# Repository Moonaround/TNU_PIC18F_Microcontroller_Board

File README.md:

# TNU PIC18F Microcontroller Board Replication

## Project Overview
This repository contains the engineering design files to replicate the **TNU PIC18F Microcontroller Board** for the Microcontrollers course footprint project. 

## Technical Specifications
* **Target Architecture:** PIC18F 40-Pin Microcontroller variant
* **Design Toolchain:** KiCad 8.0 (Ubuntu Linux environment)
* **Source Reference Assets:** 
  * Schematic Specifications: `Cadence_Pic40_TNU_PCB_schematic_v2.pdf`
  * Inventory Component Ledger: `Cadence_Pic40_TNU_Bill_Of_Material.xlsx`

## Engineering Phase Progression Log
* [x] **Phase 1-2:** Repository initialization and hardware tracking rules configuration.
* [x] **Phase 3-4:** Public cloud deployment and instructor alignment.
* [x] **Phase 5-6:** Schematic part placement and parametric BOM mapping.

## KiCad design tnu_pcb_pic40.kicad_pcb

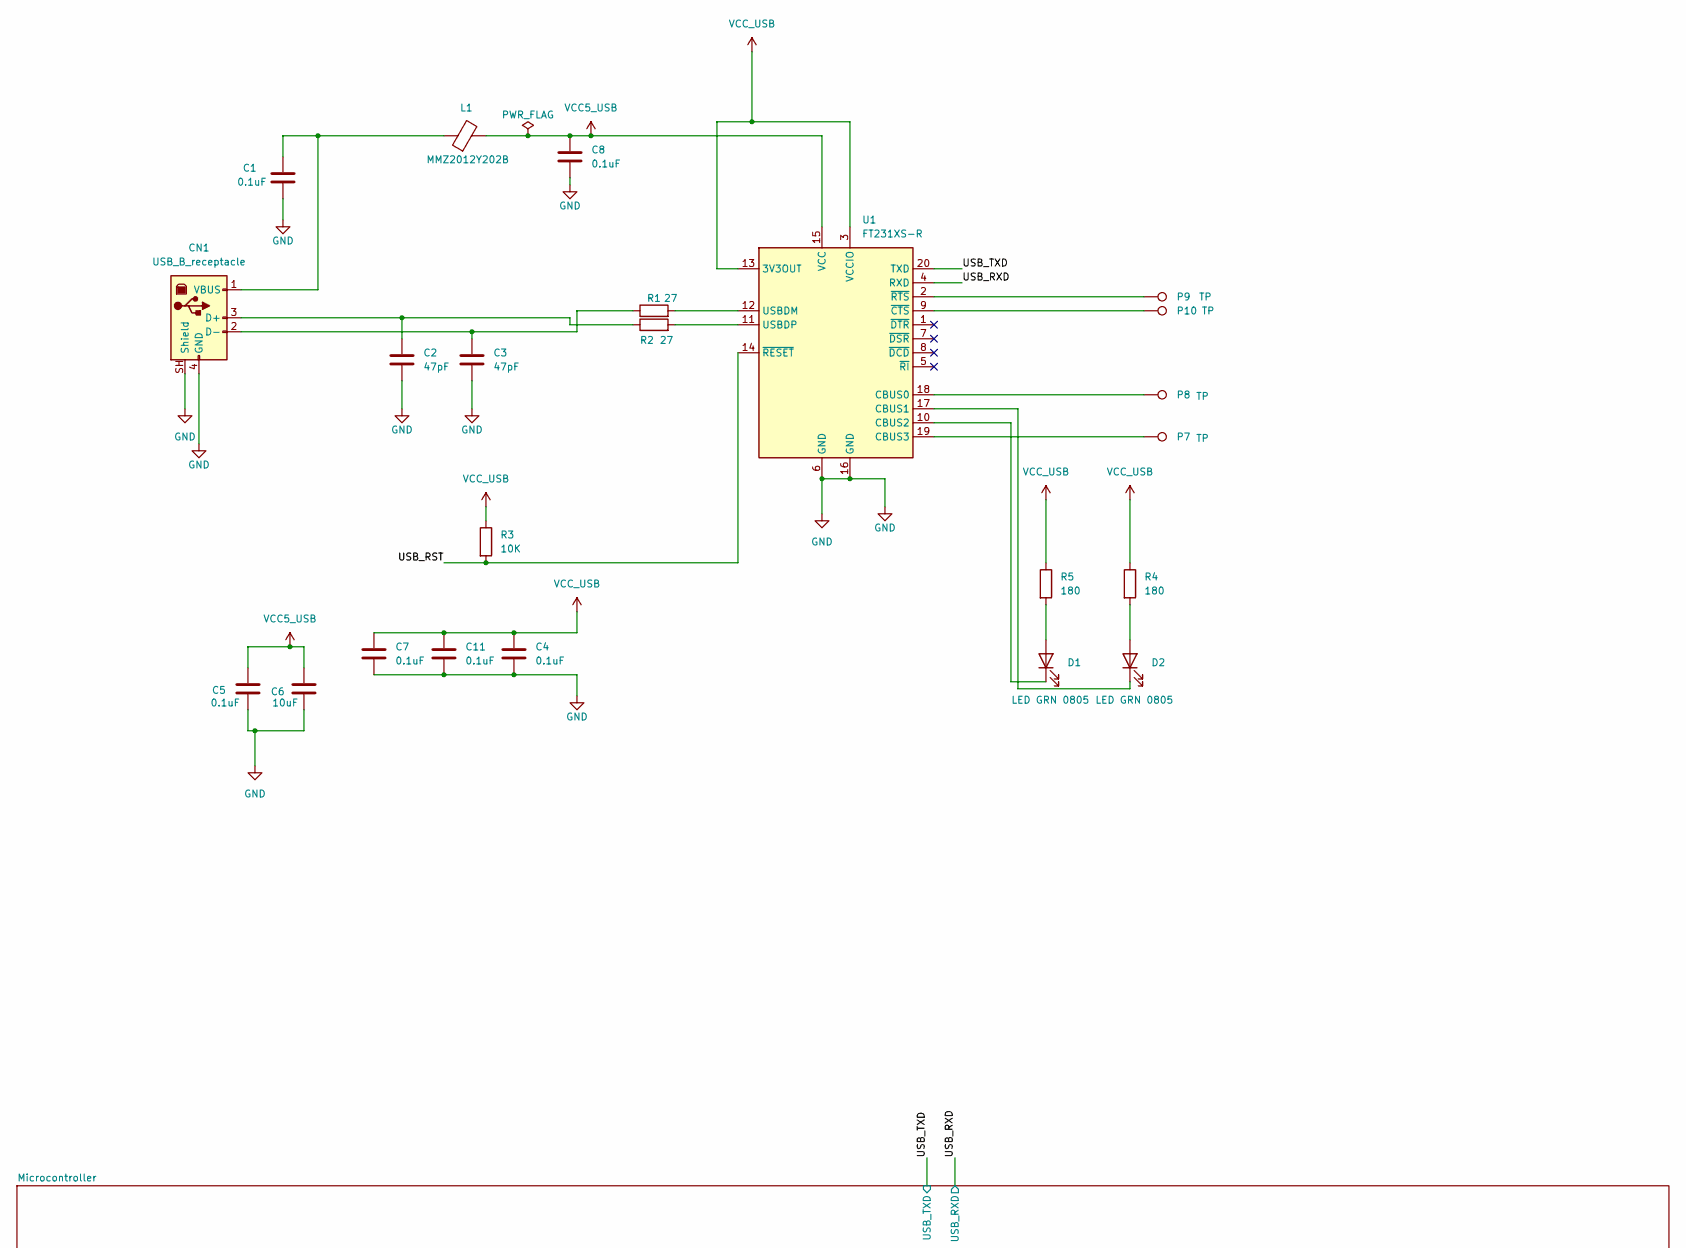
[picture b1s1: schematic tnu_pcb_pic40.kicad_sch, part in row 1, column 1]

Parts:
C1, C4, C5, C7, C8, C11: 0.1uF; C_0603_1608Metric; Manufacturer_PartNum 06033C104KAT4A
C2, C3: 47pF; C_0603_1608Metric; Manufacturer_PartNum C0603C270J5GACTU
C6: 10uF; C_1206_3216Metric; Manufacturer_PartNum GRM31CR61E106KA12L
CN1: USB_B_receptacle; USB_B_OST_USB-B1HSxx_Horizontal; Manufacturer_PartNum 897-43-004-90-000000
D1, D2: LED GRN 0805; LED_0805_2012Metric; Manufacturer_PartNum 598-8170-107F
L1: MMZ2012Y202B; L_0805_2012Metric; Manufacturer_PartNu MMZ2012Y202B
P7, P8, P9, P10: TP; TestPoint_PinHeader_1x01_P2.54mm; Manufacturer_PartNum 5006
R1, R2: 27; R_0603_1608Metric
R3: 10K; R_0603_1608Metric; Manufacturer_PartNum CRCW060310K0FKEA
R4, R5: 180; R_0603_1608Metric
U1: FT231XS-R; SSOP-20_3.9x8.7mm_P0.635mm; Manufacturer_PartNum FT231XS-R

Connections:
/USB_RST: R3.2, U1.14 (~RESET)
/USB_RXD: U1.4 (RXD); also elsewhere on the board
/USB_TXD: U1.20 (TXD); also elsewhere on the board
GND: C1.2, C2.2, C3.2, C4.2, C5.2, C6.2, C7.2, C8.2, C11.2, CN1.4 (GND), CN1.SH (Shield), U1.6 (GND), U1.16 (GND); also elsewhere on the board
unnamed: C2.1, CN1.3 (D+), R2.1
unnamed: C3.1, CN1.2 (D-), R1.1
unnamed: C1.1, CN1.1 (VBUS), L1.1
unnamed: D1.2 (A), R5.2
unnamed: D1.1 (K), U1.10 (CBUS2)
unnamed: D2.2 (A), R4.2
unnamed: D2.1 (K), U1.17 (CBUS1)
unnamed: P8.1 (1_1), U1.18 (CBUS0)
unnamed: P7.1 (1_1), U1.19 (CBUS3)
unnamed: R1.2, U1.12 (USBDM)
unnamed: R2.2, U1.11 (USBDP)
unnamed: P10.1 (1_1), U1.9 (~CTS)
unnamed: P9.1 (1_1), U1.2 (~RTS)
VCC5_USB: C5.1, C6.1, C8.1, L1.2, U1.15 (VCC); also elsewhere on the board
VCC_USB: C4.1, C7.1, C11.1, R3.1, R4.1, R5.1, U1.3 (VCCIO), U1.13 (3V3OUT)

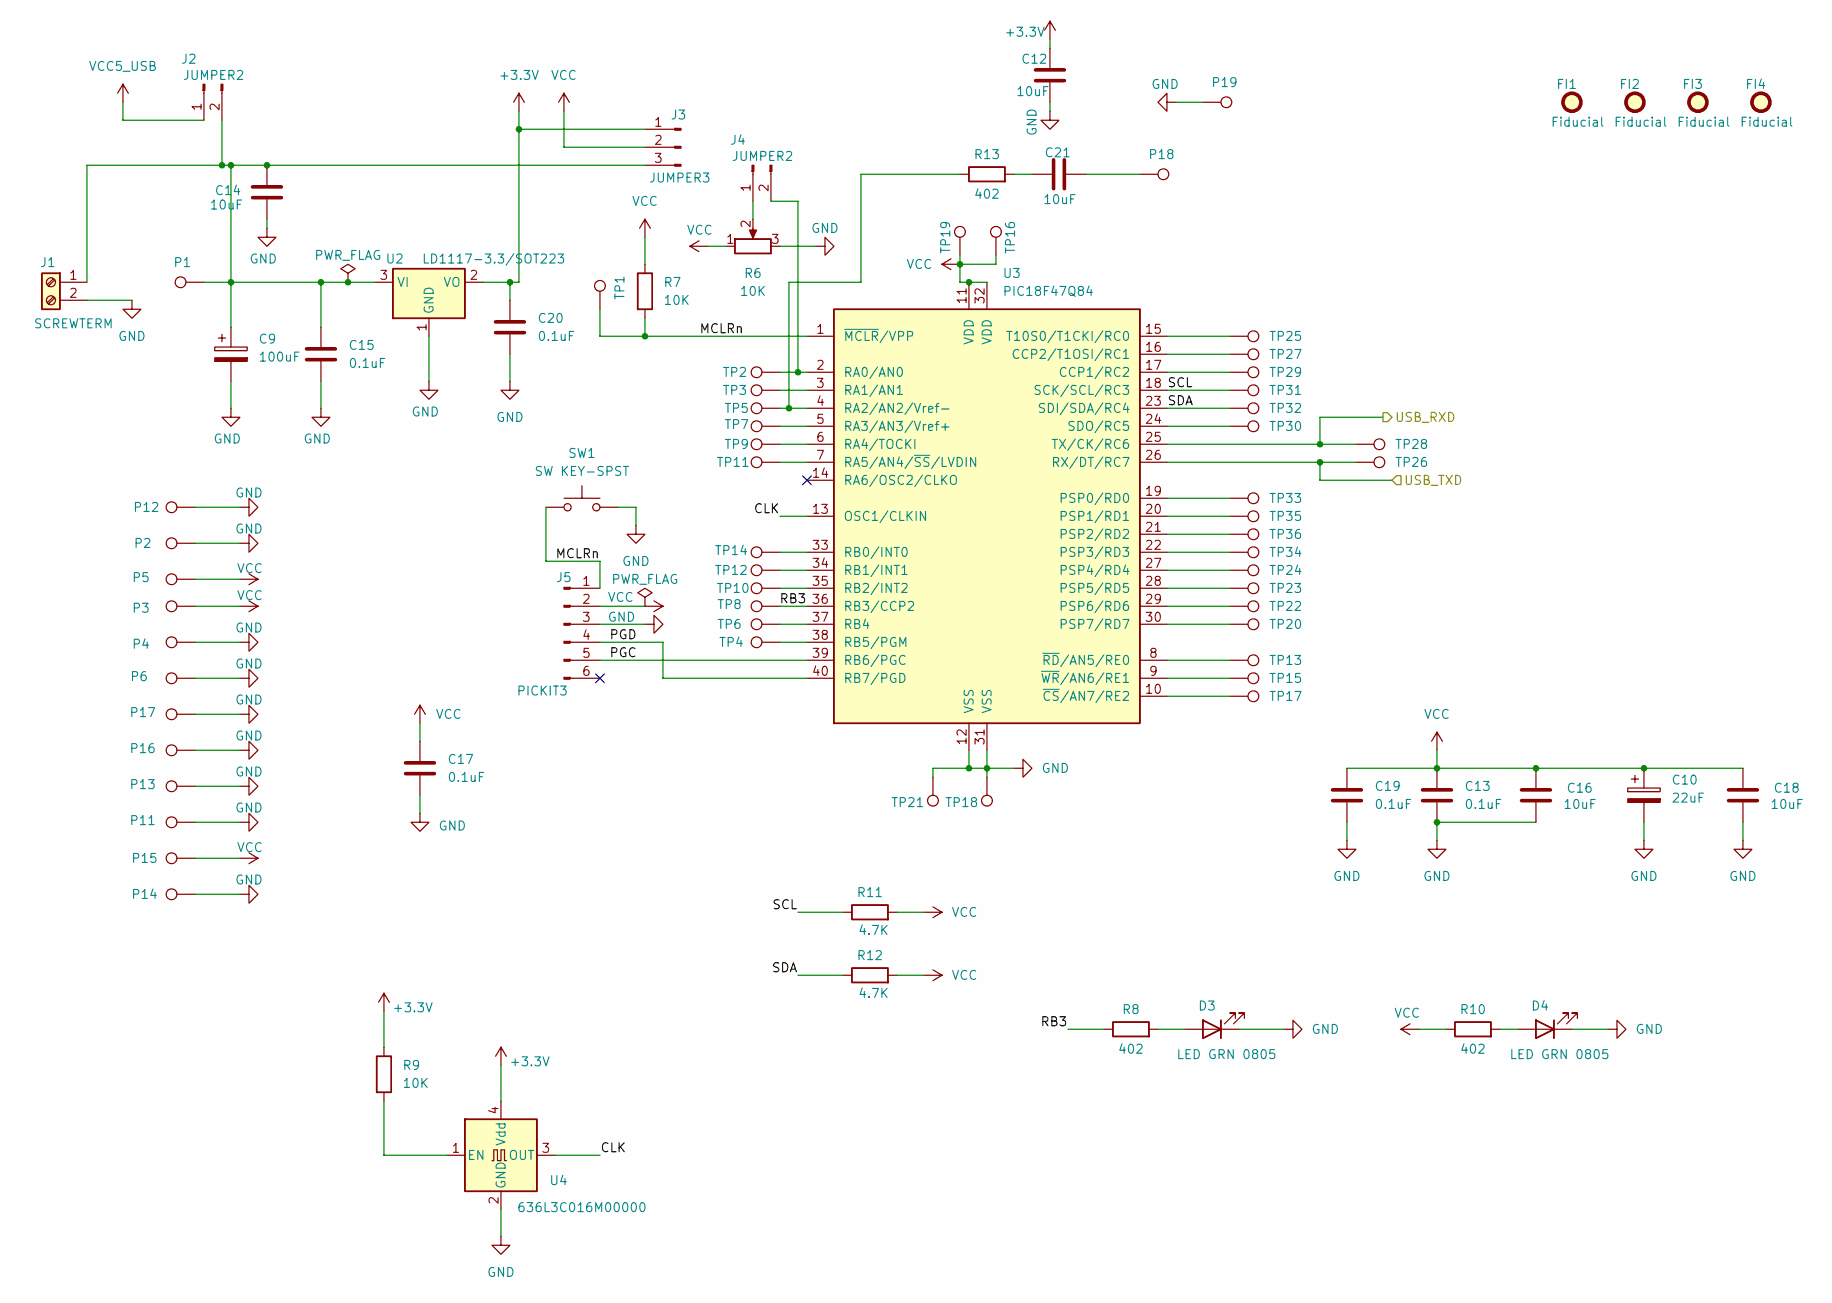
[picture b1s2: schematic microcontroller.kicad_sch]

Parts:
C9: 100uF; CP_Radial_D6.3mm_P2.50mm
C10: 22uF; CP_Elec_5x5.4; Manufacturer_PartNum EEE-FK1H220P
C12, C14, C16, C18, C21: 10uF; C_1206_3216Metric; Manufacturer_PartNum GRM31CR61E106KA12L
C13, C15, C17, C19, C20: 0.1uF; C_0603_1608Metric; Manufacturer_PartNum 06033C104KAT4A
D3, D4: LED GRN 0805; LED_0805_2012Metric; Manufacturer_PartNum 598-8170-107F
FI1, FI2, FI3, FI4: Fiducial; Fiducial_1mm_Mask2mm
J1: SCREWTERM; TerminalBlock_Phoenix_PT-1,5-2-5.0-H_1x02_P5.00mm_Horizontal
J2, J4: JUMPER2; PinHeader_1x02_P2.54mm_Vertical
J3: JUMPER3; PinHeader_1x03_P2.54mm_Vertical
J5: PICKIT3; PinHeader_1x06_P2.54mm_Vertical
P1, P2, P3, P4, P5, P6, P11, P12, P13, P14, P15, P16, P17, P18, P19: TP; TestPoint_PinHeader_1x01_P2.54mm; Manufacturer_PartNum 5006
R6: 10K; Potentiometer_Bourns_3386P_Vertical; Manufacturer_PartNum 3386P-1-103LF
R7, R9: 10K; R_0603_1608Metric; Manufacturer_PartNum CRCW060310K0FKEA
R8, R10, R13: 402; R_0603_1608Metric; Manufacturer_PartNum CRCW0603402RFKEA
R11, R12: 4.7K; R_Axial_DIN0207_L6.3mm_D2.5mm_P10.16mm_Horizontal
SW1: SW KEY-SPST; SW_PUSH-12mm
TP1, TP2, TP3, TP4, TP5, TP6, TP7, TP8, TP9, TP10, TP11, TP12, TP13, TP14, TP15, TP16, TP17, TP18, TP19, TP20, TP21, TP22, TP23, TP24, TP25, TP26, TP27, TP28, TP29, TP30, TP31, TP32, TP33, TP34, TP35, TP36: TP; TestPoint_PinHeader_1x01_P2.54mm; Manufacturer_PartNum 5006
U2: LD1117-3.3/SOT223; SOT-223-3_TabPin2
U3: PIC18F47Q84; DIP-40_W15.24mm
U4: 636L3C016M00000; Oscillator_SMD_EuroQuartz_XO53-4Pin_5.0x3.2mm; Manufacturer_PartNum 636L3C016M00000

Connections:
+3.3V: C12.1, C20.1, J3.1, R9.1, U2.2 (VO), U4.4 (Vdd)
/Microcontroller/CLK: U3.13 (OSC1/CLKIN), U4.3 (OUT)
/Microcontroller/MCLRn: J5.1, R7.2, SW1.1, TP1.1 (1_1), U3.1 (~MCLR/VPP)
/Microcontroller/PGC: J5.5, U3.39 (RB6/PGC)
/Microcontroller/PGD: J5.4, U3.40 (RB7/PGD)
/Microcontroller/RB3: R8.1, TP8.1 (1_1), U3.36 (RB3/CCP2)
/Microcontroller/SCL: R11.1, TP31.1 (1_1), U3.18 (SCK/SCL/RC3)
/Microcontroller/SDA: R12.1, TP32.1 (1_1), U3.23 (SDI/SDA/RC4)
/USB_RXD: TP28.1 (1_1), U3.25 (TX/CK/RC6); also elsewhere on the board
/USB_TXD: TP26.1 (1_1), U3.26 (RX/DT/RC7); also elsewhere on the board
GND: C9.2, C10.2, C12.2, C13.2, C14.1, C15.2, C16.1, C17.2, C18.1, C19.2, C20.2, D3.1 (K), D4.1 (K), J1.2, J5.3, P2.1 (1_1), P4.1 (1_1), P6.1 (1_1), P11.1 (1_1), P12.1 (1_1), P13.1 (1_1), P14.1 (1_1), P16.1 (1_1), P17.1 (1_1), P19.1 (1_1), R6.3, SW1.2, TP18.1 (1_1), TP21.1 (1_1), U2.1 (GND), U3.12 (VSS), U3.31 (VSS), U4.2 (GND); also elsewhere on the board
unnamed: C21.1, R13.2
unnamed: C21.2, P18.1 (1_1)
unnamed: D3.2 (A), R8.2
unnamed: D4.2 (A), R10.2
unnamed: C9.1, C14.2, C15.1, J1.1, J2.2, J3.3, P1.1 (1_1), U2.3 (VI)
unnamed: J4.1, R6.2
unnamed: J4.2, TP2.1 (1_1), U3.2 (RA0/AN0)
unnamed: TP29.1 (1_1), U3.17 (CCP1/RC2)
unnamed: TP27.1 (1_1), U3.16 (CCP2/T1OSI/RC1)
unnamed: TP33.1 (1_1), U3.19 (PSP0/RD0)
unnamed: TP35.1 (1_1), U3.20 (PSP1/RD1)
unnamed: TP36.1 (1_1), U3.21 (PSP2/RD2)
unnamed: TP34.1 (1_1), U3.22 (PSP3/RD3)
unnamed: TP24.1 (1_1), U3.27 (PSP4/RD4)
unnamed: TP23.1 (1_1), U3.28 (PSP5/RD5)
unnamed: TP22.1 (1_1), U3.29 (PSP6/RD6)
unnamed: TP20.1 (1_1), U3.30 (PSP7/RD7)
unnamed: TP3.1 (1_1), U3.3 (RA1/AN1)
unnamed: R13.1, TP5.1 (1_1), U3.4 (RA2/AN2/Vref-)
unnamed: TP7.1 (1_1), U3.5 (RA3/AN3/Vref+)
unnamed: TP9.1 (1_1), U3.6 (RA4/TOCKI)
unnamed: TP11.1 (1_1), U3.7 (RA5/AN4/~SS/LVDIN)
unnamed: TP14.1 (1_1), U3.33 (RB0/INT0)
unnamed: TP12.1 (1_1), U3.34 (RB1/INT1)
unnamed: TP10.1 (1_1), U3.35 (RB2/INT2)
unnamed: TP6.1 (1_1), U3.37 (RB4)
unnamed: TP4.1 (1_1), U3.38 (RB5/PGM)
unnamed: TP30.1 (1_1), U3.24 (SDO/RC5)
unnamed: TP25.1 (1_1), U3.15 (T10S0/T1CKI/RC0)
unnamed: TP17.1 (1_1), U3.10 (~CS/AN7/RE2)
unnamed: TP13.1 (1_1), U3.8 (~RD/AN5/RE0)
unnamed: TP15.1 (1_1), U3.9 (~WR/AN6/RE1)
unnamed: R9.2, U4.1 (EN)
VCC: C10.1, C13.1, C16.2, C17.1, C18.2, C19.1, J3.2, J5.2, P3.1 (1_1), P5.1 (1_1), P15.1 (1_1), R6.1, R7.1, R10.1, R11.2, R12.2, TP16.1 (1_1), TP19.1 (1_1), U3.11 (VDD), U3.32 (VDD)
VCC5_USB: J2.1; also elsewhere on the board

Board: 2 copper layers, 113 parts (0 on the bottom side), 61 nets, no tracks yet.

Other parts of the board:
H1, H2, H3, H4: MountingHole_3.2mm_M3_Pad

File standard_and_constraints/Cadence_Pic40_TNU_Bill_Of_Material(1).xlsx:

Item Number | Quantity | Value | Description | Part Number | Part Reference | Manufacturer | Manufacturer_PartNum | Manufacturer2 | Manufacturer2_PartNum | Distributor | Distributor_PartNum | Distributor2 | Distributor2_PartNum | DigiKey | PCB Footprint
1 | 11 | 0.1uF | CAP .1UF 25V CERAMIC X7R 0603 | 13322 | C1 C4 C5 C7 C8 C11 C13 C15 C17 C19 C20 | AVX | 06033C104KAT4A |  |  | Mouser | 581-06033C104KAT4A |  |  |  | cap0603
2 | 2 | 47pF | CAP CER 47PF 50V 0603 | CAP47pF_0603 | C2 C3 | Kemet | C0603C270J5GACTU | AVX | 06035A270JAT2A | Digikey | 399-1054-1-ND |  |  | 399-1054-1-ND | cap0603
3 | 6 | 10uF | CAP 10UF 25V CERAMIC X5R 1206 | 15434 | C6 C12 C14 C16 C18 C21 | Murata | GRM31CR61E106KA12L |  |  |  |  |  |  | 490-3373-1-ND | cap1206
4 | 1 | 100uF |  |  | C9 |  |  |  |  |  |  |  |  |  | ecap2
5 | 1 | 22uF | CAP 22UF 50V ELECT FC SMD | 11524 | C10 | Panasonic | EEE-FK1H220P | Nichicon | UUD1H220MCL1GS | Digikey | PCE3811CT-ND | Mouser | 667-EEE-FK1H220P | PCE3811CT-ND | SME22CAP
6 | 1 | USB | USB B receptacle | 15256 | CN1 | Mill-Max | 897-43-004-90-000000 |  |  | Digikey | ED90064-ND |  |  | ED90064-ND | usb_b_receptacle
7 | 4 | LED GRN 0805 | LED ALINGAP GRN CLEAR 0805 SMD | 19511 | D1 D2 D3 D4 | Dialight | 598-8170-107F |  |  | Digikey | 350-2044-1-ND | Mouser | 645-598-8170-107F | 350-2044-1-ND | LED0805
8 | 1 | Fiducial |  |  | FI1 |  |  |  |  |  |  |  |  |  | fiducial_1mm_round
9 | 1 | Fiducial |  |  | FI2 |  |  |  |  |  |  |  |  |  | fiducial_1mm_round
10 | 1 | Fiducial |  |  | FI3 |  |  |  |  |  |  |  |  |  | fiducial_1mm_round
11 | 1 | Fiducial |  |  | FI4 |  |  |  |  |  |  |  |  |  | fiducial_1mm_round
12 | 1 | SCREWTERM |  |  | J1 |  |  |  |  |  |  |  |  |  | W237-102
13 | 1 | JUMPER2 |  |  | J2 |  |  |  |  |  |  |  |  |  | JUMPER2
14 | 1 | JUMPER3 |  |  | J3 |  |  |  |  |  |  |  |  |  | JUMPER3
15 | 1 | JUMPER2 |  |  | J4 |  |  |  |  |  |  |  |  |  | JUMPER2
16 | 1 | PICKIT3 |  |  | J5 |  |  |  |  |  |  |  |  |  | HEADER6_SINGLE
17 | 1 | MMZ2012Y202B | Ferrite, 100Mhz, 0805, 400mA | 15850 | L1 | TDK | MMZ2012Y202B |  |  | Digikey | 445-1561-1-ND |  |  | 445-1561-1-ND | res0805
18 | 55 | TP | TEST POINT PC COMPACT .063"D BLK | 12119 | P1 P2 P3 P4 P5 P6 P7 P8 P9 P10 P11 P12 P13 P14 P15 P16 P17 P18 P19 TP1 TP2 TP3 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 | Keystone | 5006 |  |  | Digikey | 5006K-ND |  |  | 5006K-ND | TESTPT
19 | 2 | 27 | RES 27 1/16W 5% 0603 | RES27_0603 | R1 R2 |  |  |  |  |  |  |  |  |  | res0603
20 | 3 | 10K | RES 10k 1/16W 1% 0603 | 13324 | R3 R7 R9 | Vishay | CRCW060310K0FKEA |  |  | Digikey | 541-10.0KHCT-ND |  |  | 541-10.0KHCT-ND | RES0603
21 | 2 | 180 | RES 180 1/16W 5% 0603 | RES180_0603 | R4 R5 |  |  |  |  |  |  |  |  |  | res0603
22 | 1 | 10K |  |  | R6 |  |  |  |  |  |  |  |  |  | POT3386PorF
23 | 3 | 402 | RES 402 1/16W 1% 0603 | 13606 | R8 R10 R13 | Vishay | CRCW0603402RFKEA |  |  | Digikey | 541-402HCT-ND |  |  | 541-402HCT-ND | res0603
24 | 1 | 4.7K |  |  | R11 |  |  |  |  |  |  |  |  |  | RES500
25 | 1 | 4.7K |  |  | R12 |  |  |  |  |  |  |  |  |  | RES500
26 | 1 | SW KEY-SPST |  |  | SW1 |  |  |  |  |  |  |  |  |  | tactile-pth-12mm
27 | 1 | FT231XS-R | FTDI Chip FT231XS-R, Interface RS232, RS422, RS485, SIE, UART 3MBd, 5 V, 20-pin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 |  | U1 |  |  |  |  |  |  |  |  |  | SSOP20
28 | 1 | LD1117-3.3/SOT223 |  |  | U2 |  |  |  |  |  |  |  |  |  | SOT223NEW
29 | 1 | PIC18F47Q84 |  |  | U3 |  |  |  |  |  |  |  |  |  | DIP40_6
30 | 1 | 636L3C016M00000 | OSCILLATOR XO 16MHZ 3.3V SMD | 21108 | U4 | CTS | 636L3C016M00000 |  |  | Digikey | CTX691CT-ND |  |  | CTX691CT-ND | CTS636

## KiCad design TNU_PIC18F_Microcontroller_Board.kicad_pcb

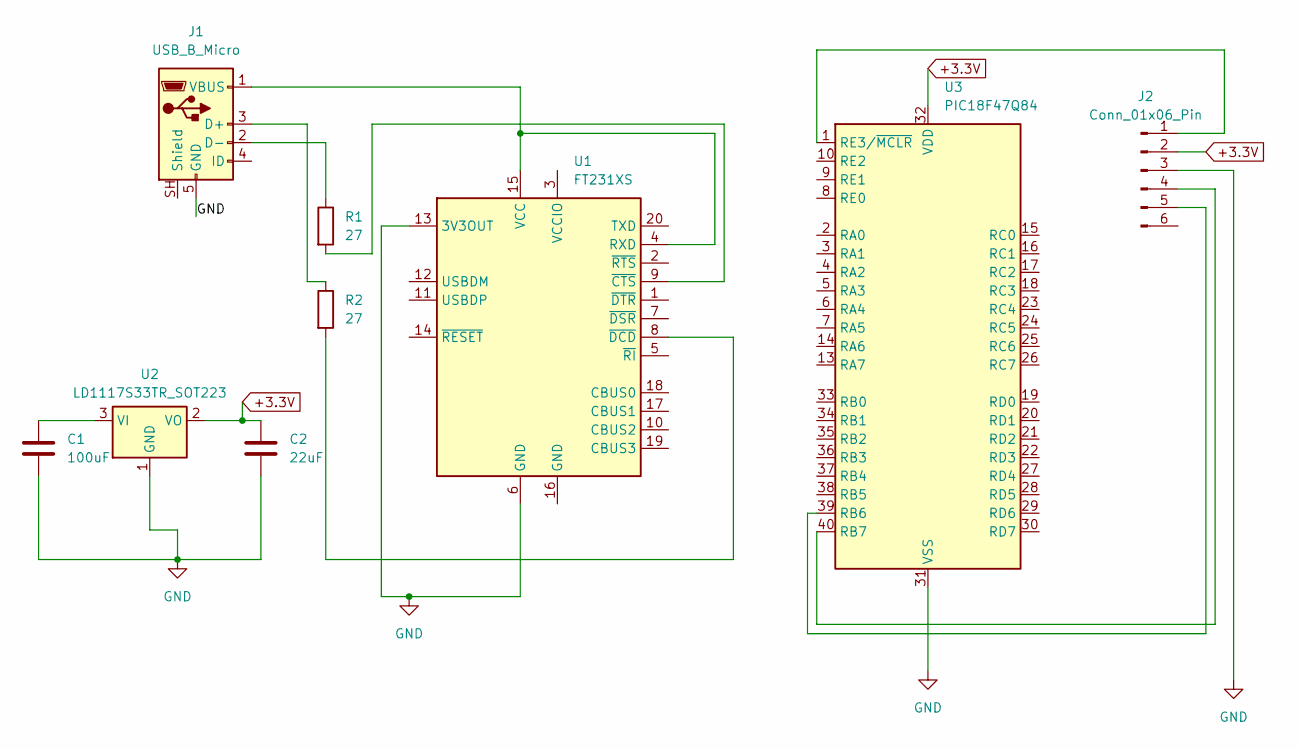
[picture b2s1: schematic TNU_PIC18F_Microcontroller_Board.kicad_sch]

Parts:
C1: 100uF; C_0805_2012Metric
C2: 22uF; C_0805_2012Metric
J1: USB_B_Micro; USB_Micro-B_Amphenol_10103594-0001LF_Horizontal
J2: Conn_01x06_Pin; PinHeader_1x06_P2.54mm_Vertical
R1, R2: 27; R_0805_2012Metric
U1: FT231XS; SSOP-20_3.9x8.7mm_P0.635mm
U2: LD1117S33TR_SOT223; SOT-223-3_TabPin2
U3: PIC18F47Q84; DIP-40_W15.24mm

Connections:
+3.3V: C2.1, J2.2, U2.2 (VO), U3.11 (VDD), U3.32 (VDD)
GND: C1.2, C2.2, J1.5 (GND), J2.3, U1.6 (GND), U1.13 (3V3OUT), U2.1 (GND), U3.12 (VSS), U3.31 (VSS)
unnamed: J1.3 (D+), R2.1
unnamed: J1.2 (D-), R1.1
unnamed: J1.1 (VBUS), U1.4 (RXD), U1.15 (VCC)
unnamed: J2.1, U3.1 (RE3/~MCLR)
unnamed: J2.4, U3.40 (RB7)
unnamed: J2.5, U3.39 (RB6)
unnamed: R1.2, U1.9 (~CTS)
unnamed: R2.2, U1.8 (~DCD)
unnamed: C1.1, U2.3 (VI)

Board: 2 copper layers, 9 parts (0 on the bottom side), 11 nets, no tracks yet.
